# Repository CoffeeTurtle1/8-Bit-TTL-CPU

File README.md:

# 8-Bit TTL CPU
The goal of this project is to design (and hopefully build) a fully functional TTL CPU using 7400 series logic chips.

# The Architecture
This cpu has two RAM chips. One 256x8 RAM chip for holding data and a 65536x24 program memory chip.

## Registers
|  Register | Description |
|  ------ | ------ |
|  Program Counter (PC) | Holds the address of the next instruction to be executed |
|  Instruction Register | Holds the current instruction being executed |
|  Carry Flag | Holds the carry bit |
|  RA | General purpose register |
|  RB | General purpose register / Accumulator |

## Instruction Set
|  Address (16-bit) | Data (8-bit) | Op-Code | Instruction | Description |
|  ------ | ------ | ------ | ------ | ------ |
|  0000000000000000 | 00000000 | 0001 | ADD | Stores the sum of RA and RB in RB |
|  0000000000000000 | 00000000 | 0010 | SUB | Stores the result of RA minus RB in RB |
|  0000000000000000 | 00000000 | 0011 | JMP | Sets the value of the PC to the value of the address bits |
|  0000000000000000 | 00000000 | 0100 | JC | If the carry register is set to one the PC is set to the value of the address bits |
|  0000000000000000 | 00000000 | 0101 | LDB | Stores the value stored at the location pointed to by RA in RB |
|  0000000000000000 | 00000000 | 0110 | STB | Stores the value in RB at the location pointed to by RA |
|  0000000000000000 | 00000000 | 0111 | PUT | Stores the data bits in RB |
|  0000000000000000 | 00000000 | 1000 | INP | Stores the current value on the I/O bus in RB |
|  0000000000000000 | 00000000 | 1001 | OUT | Sets the I/O bus to the value of RB |
|  0000000000000000 | 00000000 | 1111 | HLT | Halts the CPU |

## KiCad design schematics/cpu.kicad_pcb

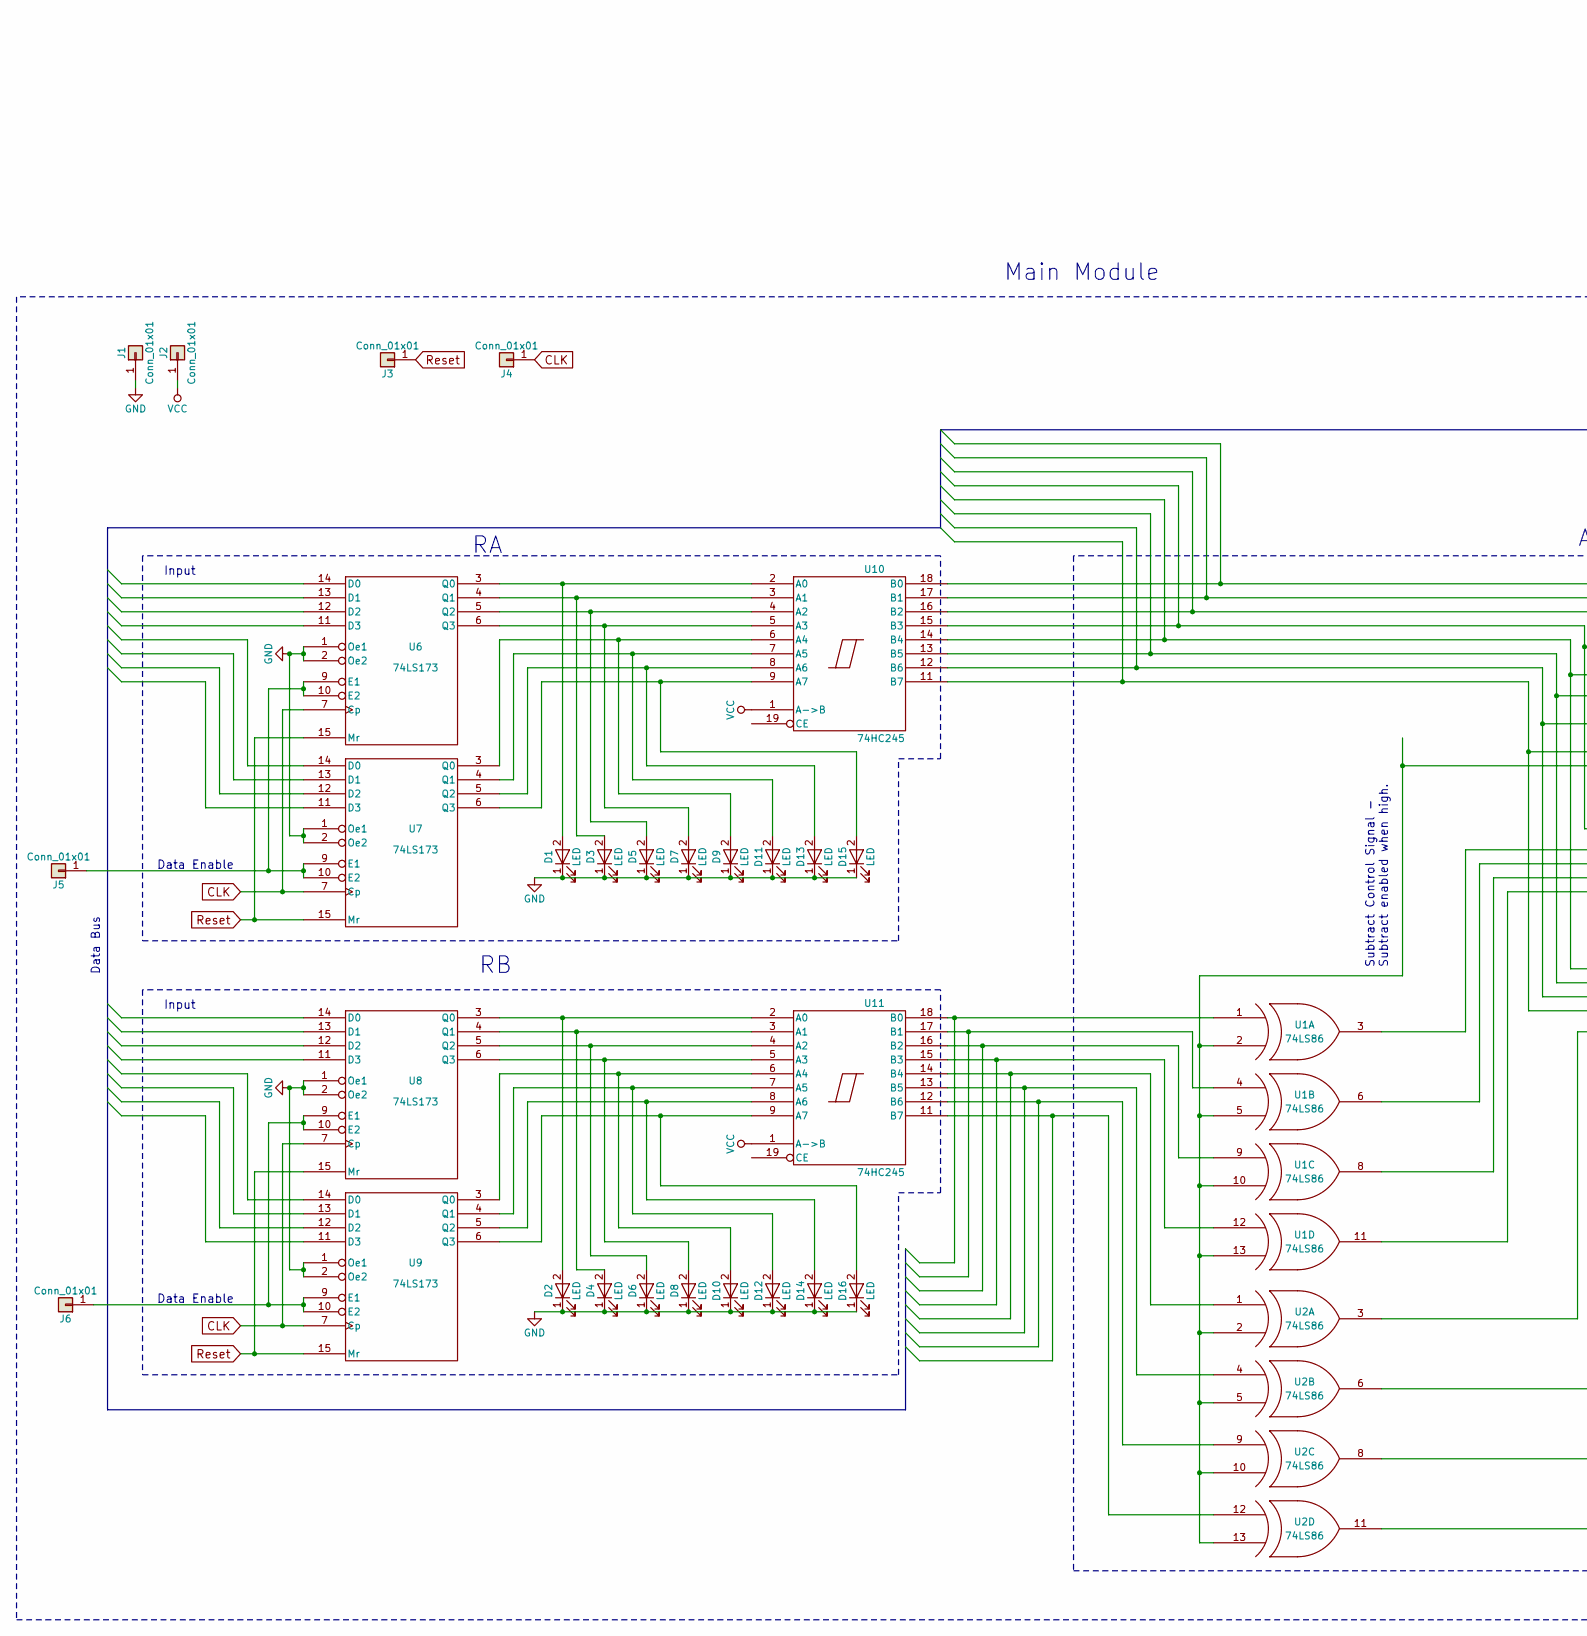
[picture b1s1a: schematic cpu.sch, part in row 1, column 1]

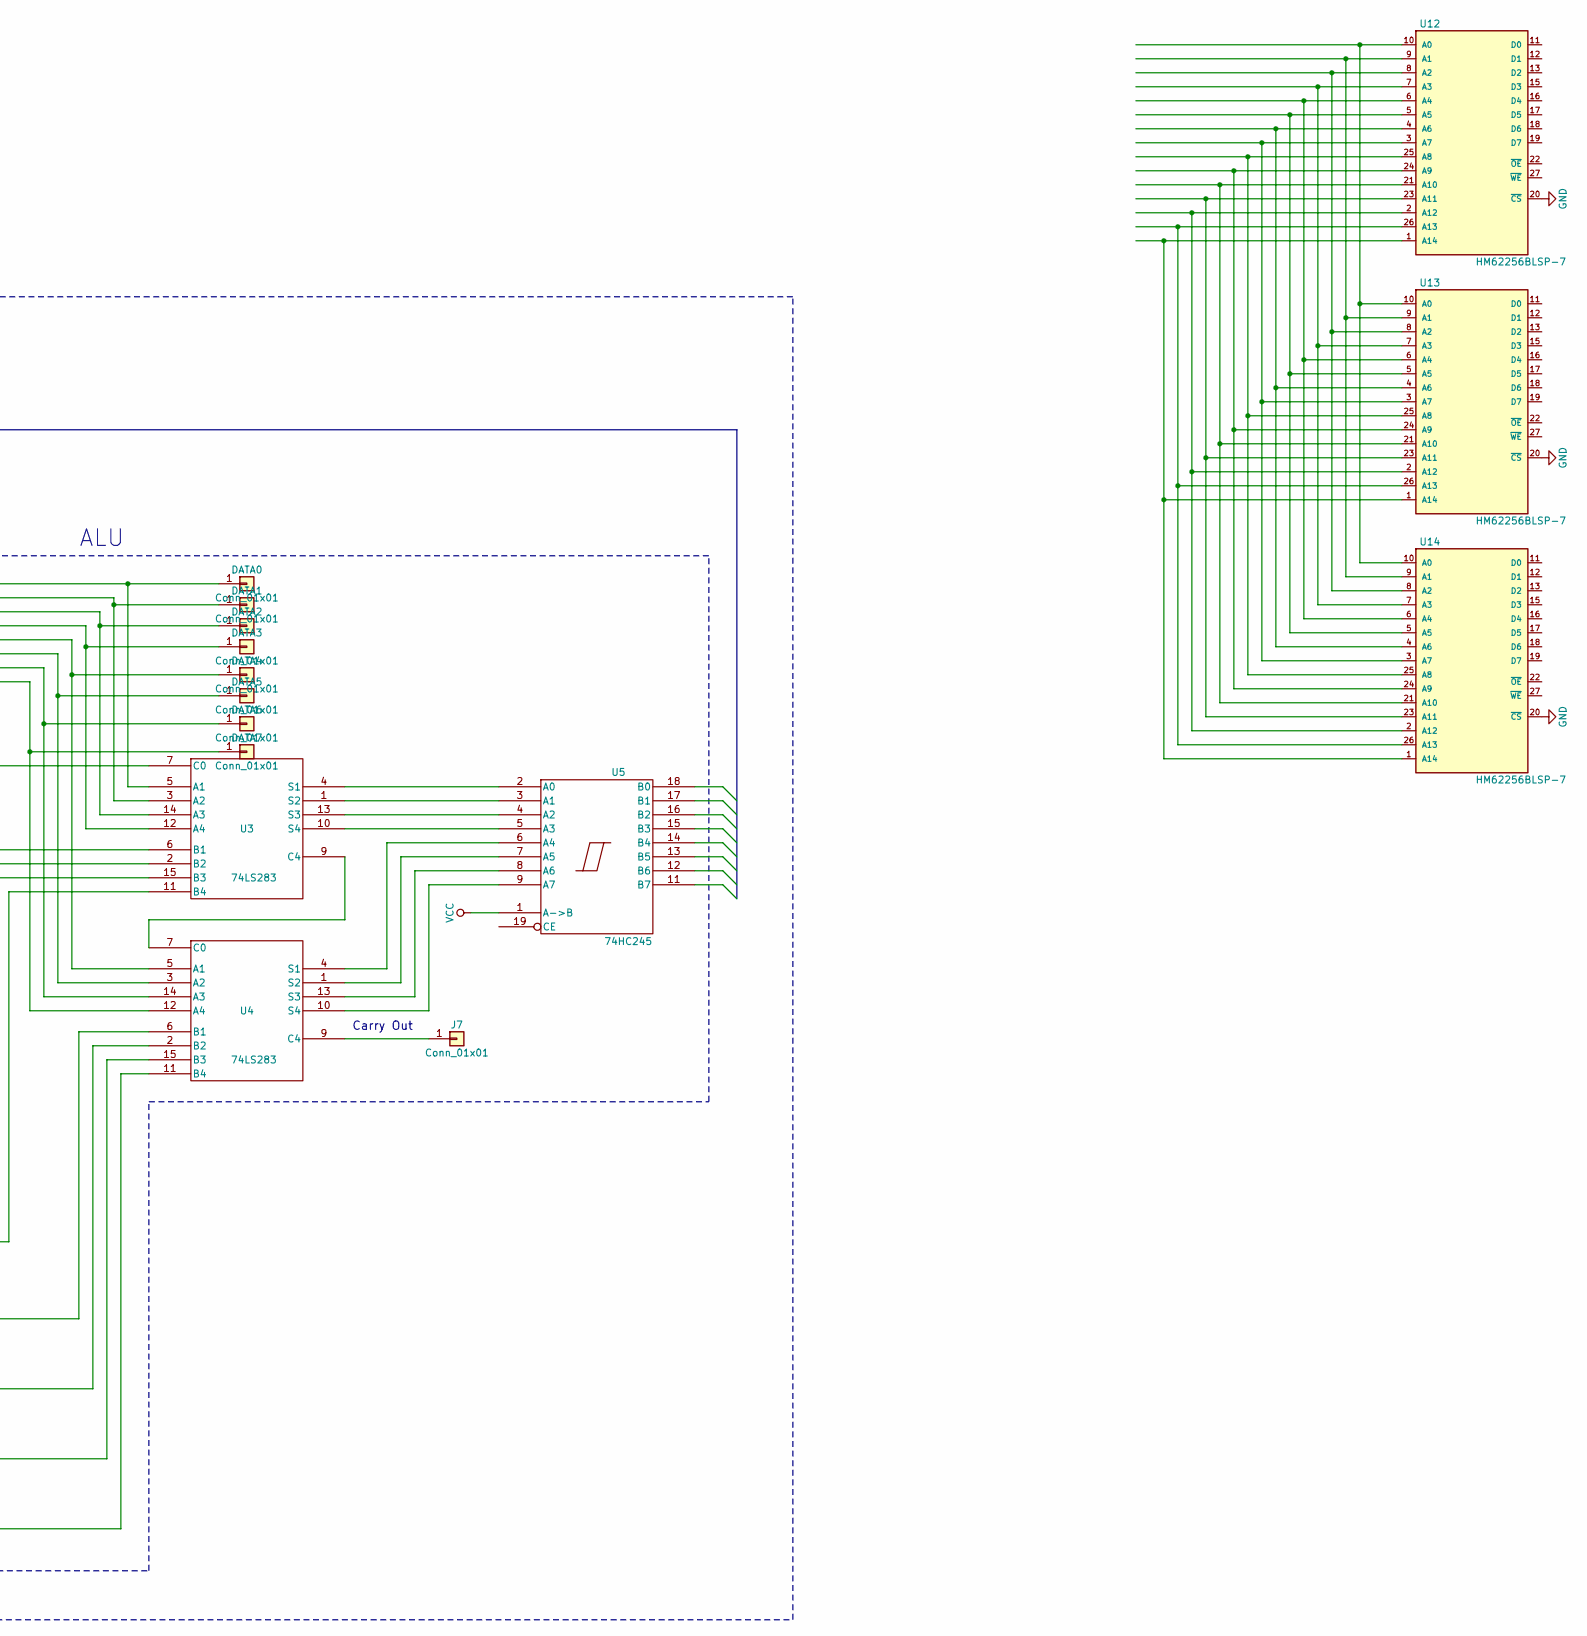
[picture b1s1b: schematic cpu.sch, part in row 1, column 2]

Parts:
D1, D2, D3, D4, D5, D6, D7, D8, D9, D10, D11, D12, D13, D14, D15, D16: LED; LED_D3.0mm
DATA0, DATA1, DATA3, DATA4, DATA5, DATA6, DATA7: Conn_01x01; Pin_Header_Straight_1x01_Pitch2.00mm
DATA2: Pin_Header_Straight_1x01_Pitch2.00mm
J1, J2, J3, J4, J5, J6, J7: Conn_01x01; Pin_Header_Straight_1x01_Pitch2.00mm
U1, U2: 74LS86; DIP-14_W7.62mm
U3, U4: 74LS283; DIP-16_W7.62mm
U5, U10, U11: 74HC245; DIP-20_W7.62mm
U6, U7, U8, U9: 74LS173; DIP-16_W7.62mm
U12, U13, U14: HM62256BLSP-7

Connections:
CLK: J4.1, U6.7 (Cp), U7.7 (Cp), U8.7 (Cp), U9.7 (Cp)
GND: D1.1 (K), D2.1 (K), D3.1 (K), D4.1 (K), D5.1 (K), D6.1 (K), D7.1 (K), D8.1 (K), D9.1 (K), D10.1 (K), D11.1 (K), D12.1 (K), D13.1 (K), D14.1 (K), D15.1 (K), D16.1 (K), J1.1, U1.7 (GND), U2.7 (GND), U3.8 (GND), U4.8 (GND), U5.10 (GND), U6.1 (Oe1), U6.2 (Oe2), U6.8 (GND), U7.1 (Oe1), U7.2 (Oe2), U7.8 (GND), U8.1 (Oe1), U8.2 (Oe2), U8.8 (GND), U9.1 (Oe1), U9.2 (Oe2), U9.8 (GND), U10.10 (GND), U11.10 (GND), U12.20 (~CS), U13.20 (~CS), U14.20 (~CS)
unnamed: D1.2 (A), U6.3 (Q0), U10.2 (A0)
unnamed: D2.2 (A), U8.3 (Q0), U11.2 (A0)
unnamed: D3.2 (A), U6.4 (Q1), U10.3 (A1)
unnamed: D4.2 (A), U8.4 (Q1), U11.3 (A1)
unnamed: D5.2 (A), U6.5 (Q2), U10.4 (A2)
unnamed: D6.2 (A), U8.5 (Q2), U11.4 (A2)
unnamed: D7.2 (A), U6.6 (Q3), U10.5 (A3)
unnamed: D8.2 (A), U8.6 (Q3), U11.5 (A3)
unnamed: D9.2 (A), U7.3 (Q0), U10.6 (A4)
unnamed: D10.2 (A), U9.3 (Q0), U11.6 (A4)
unnamed: D11.2 (A), U7.4 (Q1), U10.7 (A5)
unnamed: D12.2 (A), U9.4 (Q1), U11.7 (A5)
unnamed: D13.2 (A), U7.5 (Q2), U10.8 (A6)
unnamed: D14.2 (A), U9.5 (Q2), U11.8 (A6)
unnamed: D15.2 (A), U7.6 (Q3), U10.9 (A7)
unnamed: D16.2 (A), U9.6 (Q3), U11.9 (A7)
unnamed: DATA0.1, U3.5 (A1), U10.18 (B0)
unnamed: DATA1.1, U3.3 (A2), U10.17 (B1)
unnamed: DATA2.1, U3.14 (A3), U10.16 (B2)
unnamed: DATA3.1, U3.12 (A4), U10.15 (B3)
unnamed: DATA4.1, U4.5 (A1), U10.14 (B4)
unnamed: DATA5.1, U4.3 (A2), U10.13 (B5)
unnamed: DATA6.1, U4.14 (A3), U10.12 (B6)
unnamed: DATA7.1, U4.12 (A4), U10.11 (B7)
unnamed: J5.1, U6.9 (E1), U6.10 (E2), U7.9 (E1), U7.10 (E2)
unnamed: J6.1, U8.9 (E1), U8.10 (E2), U9.9 (E1), U9.10 (E2)
unnamed: J7.1, U4.9 (C4)
unnamed: U1.1 (IN1), U11.18 (B0)
unnamed: U1.3 (OUT), U3.6 (B1)
unnamed: U1.4 (IN1), U11.17 (B1)
unnamed: U1.6 (OUT), U3.2 (B2)
unnamed: U1.8 (OUT), U3.15 (B3)
unnamed: U1.9 (IN1), U11.16 (B2)
unnamed: U1.2 (IN2), U1.5 (IN2), U1.10 (IN2), U1.13 (IN2), U2.2 (IN2), U2.5 (IN2), U2.10 (IN2), U2.13 (IN2), U3.7 (C0)
unnamed: U1.11 (OUT), U3.11 (B4)
unnamed: U1.12 (IN1), U11.15 (B3)
unnamed: U2.3 (OUT), U4.6 (B1)
unnamed: U2.6 (OUT), U4.2 (B2)
unnamed: U2.8 (OUT), U4.15 (B3)
unnamed: U2.11 (OUT), U4.11 (B4)
unnamed: U3.1 (S2), U5.3 (A1)
unnamed: U3.4 (S1), U5.2 (A0)
unnamed: U3.9 (C4), U4.7 (C0)
unnamed: U3.10 (S4), U5.5 (A3)
unnamed: U3.13 (S3), U5.4 (A2)
unnamed: U4.1 (S2), U5.7 (A5)
unnamed: U4.4 (S1), U5.6 (A4)
unnamed: U4.10 (S4), U5.9 (A7)
unnamed: U4.13 (S3), U5.8 (A6)
unnamed: U2.12 (IN1), U11.11 (B7)
unnamed: U2.9 (IN1), U11.12 (B6)
unnamed: U2.4 (IN1), U11.13 (B5)
unnamed: U2.1 (IN1), U11.14 (B4)
unnamed: U12.1 (A14), U13.1 (A14), U14.1 (A14)
unnamed: U12.2 (A12), U13.2 (A12), U14.2 (A12)
unnamed: U12.3 (A7), U13.3 (A7), U14.3 (A7)
unnamed: U12.4 (A6), U13.4 (A6), U14.4 (A6)
unnamed: U12.5 (A5), U13.5 (A5), U14.5 (A5)
unnamed: U12.6 (A4), U13.6 (A4), U14.6 (A4)
unnamed: U12.7 (A3), U13.7 (A3), U14.7 (A3)
unnamed: U12.8 (A2), U13.8 (A2), U14.8 (A2)
unnamed: U12.9 (A1), U13.9 (A1), U14.9 (A1)
unnamed: U12.10 (A0), U13.10 (A0), U14.10 (A0)
unnamed: U12.21 (A10), U13.21 (A10), U14.21 (A10)
unnamed: U12.23 (A11), U13.23 (A11), U14.23 (A11)
unnamed: U12.24 (A9), U13.24 (A9), U14.24 (A9)
unnamed: U12.25 (A8), U13.25 (A8), U14.25 (A8)
unnamed: U12.26 (A13), U13.26 (A13), U14.26 (A13)
Reset: J3.1, U6.15 (Mr), U7.15 (Mr), U8.15 (Mr), U9.15 (Mr)
VCC: J2.1, U1.14 (VCC), U2.14 (VCC), U3.16 (VCC), U4.16 (VCC), U5.1 (A->B), U5.20 (VCC), U6.16 (VCC), U7.16 (VCC), U8.16 (VCC), U9.16 (VCC), U10.1 (A->B), U10.20 (VCC), U11.1 (A->B), U11.20 (VCC)

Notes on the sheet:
Data Enable
Input
Subtract Control Signal - Subtract enabled when high.
Carry Out
ALU
Data Bus
Main Module

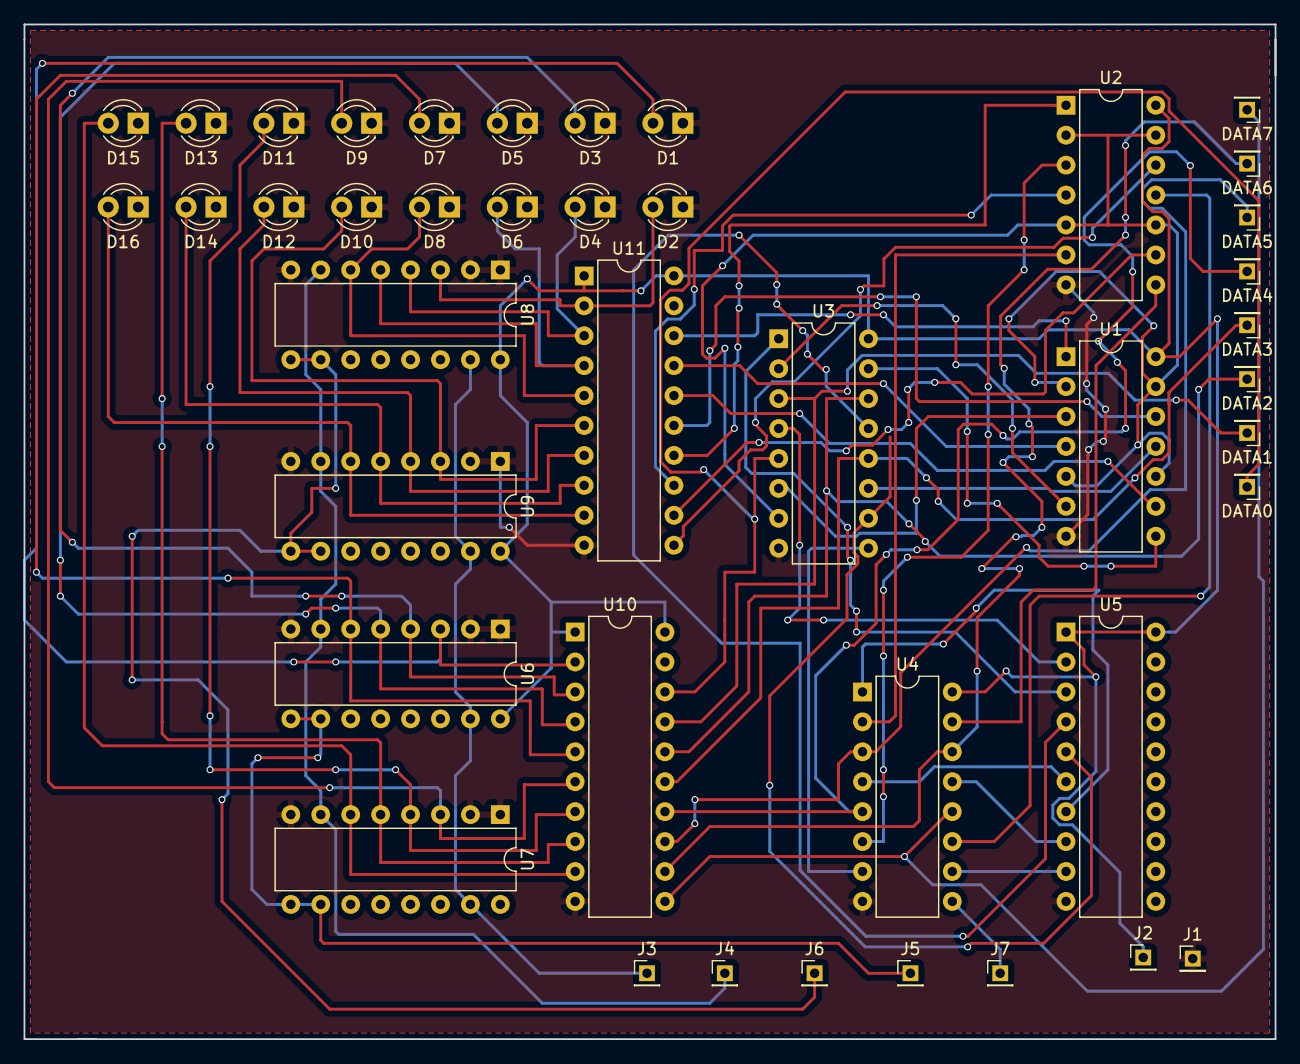
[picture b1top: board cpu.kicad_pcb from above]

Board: 2 copper layers, 106.2 x 86.1 mm, 42 parts (0 on the bottom side), 57 nets.

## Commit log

2018-09-09 Renamed folder to schematics
2018-09-20 Started Designing the pcb for the ALU and GP registers.
2018-10-02 Change STA to STB
2018-10-03 Finished placing tracks for the registers and ALU PCB.
2018-10-03 Change LDA to LDB
